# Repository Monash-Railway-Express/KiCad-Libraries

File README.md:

# KiCad-Libraries
To add the footprint library, go to Assign footprints ->  Manage footprint libraries -> Add existing library and select the MREx.pretty folder. Alternatively, from the main KiCad project go to Preferences ->  Manage footprint libraries -> Add existing library and select the MREx.pretty folder. The library “MREx” will then appear in the footprint library list and you will be able to access its footprints in Assign footprints. When updates are made to the library, pull origin in the cloned repo (clone this repo) and KiCad will use the updated library automatically.

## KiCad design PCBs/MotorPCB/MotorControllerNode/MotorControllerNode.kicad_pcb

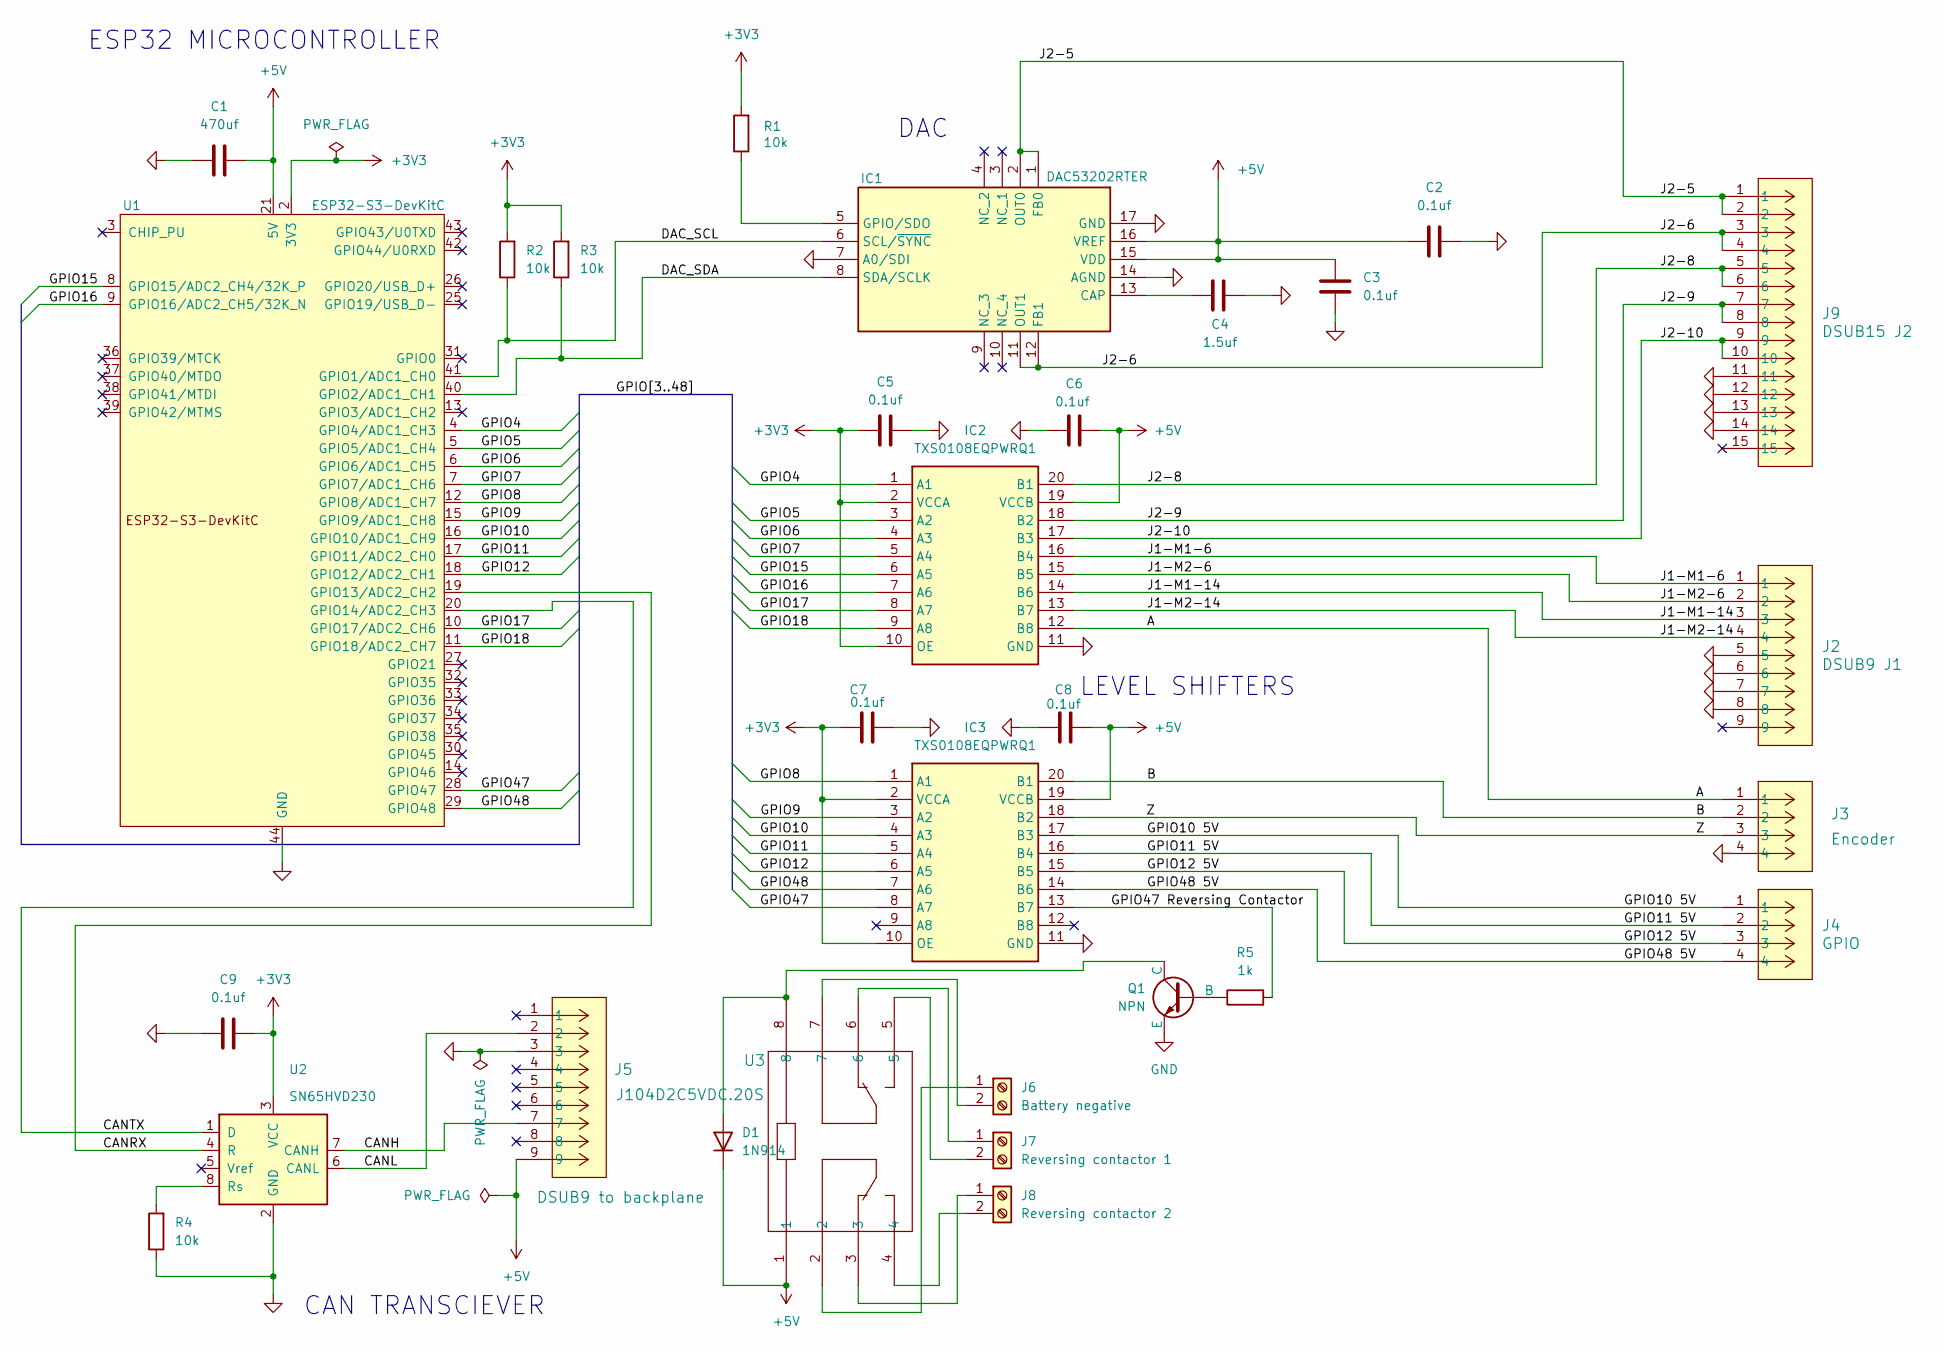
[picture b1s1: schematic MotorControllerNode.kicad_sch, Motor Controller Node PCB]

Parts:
C1: 470uf; C_Radial_D8.0mm_H11.5mm_P3.50mm
C2, C3, C5, C6, C7, C8, C9: 0.1uf; C_0603_1608Metric
C4: 1.5uf; C_0603_1608Metric
D1: 1N914; D_DO-35_SOD27_P7.62mm_Horizontal
IC1: DAC53202RTER; Texas_RTE0016D_WQFN-16-1EP_3x3mm_P0.5mm_EP0.8x0.8mm; Manufacturer_Part_Number DAC53202RTER; Mouser Part Number 595-DAC53202RTER
IC2, IC3: TXS0108EQPWRQ1; SOP65P640X120-20N; Manufacturer_Part_Number TXS0108EQPWRQ1; Mouser Part Number 595-TXS0108EQPWRQ1
J2: DSUB9 J1; DSUB9_FEMALE_RIGHT-ANGLE-THT_2301844-1_TEC
J3: Encoder; SCREW-TERMINAL_2.54mm_1725672_PXC
J4: GPIO; SCREW-TERMINAL_2.54mm_1725672_PXC
J5: DSUB9 to backplane; DSUB9_FEMALE_RIGHT-ANGLE-THT_2301844-1_TEC
J6: Battery negative; TerminalBlock_CUI_TB007-508-02_1x02_P5.08mm_Horizontal
J7: Reversing contactor 1; TerminalBlock_CUI_TB007-508-02_1x02_P5.08mm_Horizontal
J8: Reversing contactor 2; TerminalBlock_CUI_TB007-508-02_1x02_P5.08mm_Horizontal
J9: DSUB15 J2; DSUB15_FEMALE_RIGHT-ANGLE-THT_A-HDF15A-KG-TAXB
Q1: NPN; TO-92
R1, R2, R3, R4: 10k; R_0603_1608Metric
R5: 1k; R_0603_1608Metric_Pad0.98x0.95mm_HandSolder
U1: ESP32-S3-DevKitC
U2: SN65HVD230; SOIC-8_3.9x4.9mm_P1.27mm
U3: J104D2C5VDC.20S; RELAY8_J104D2C5VDC.20S_CRS

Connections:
+3V3: C5.1, C7.1, C9.2, IC2.2 (VCCA), IC2.10 (OE), IC3.2 (VCCA), IC3.10 (OE), R1.2, R2.2, R3.2, U1.1 (3V3), U1.2 (3V3), U2.3 (VCC)
+5V: C1.2, C2.1, C3.1, C6.2, C8.2, D1.1 (K), IC1.15 (VDD), IC1.16 (VREF), IC2.19 (VCCB), IC3.19 (VCCB), J5.9, U1.21 (5V), U3.1
/A: IC2.12 (B8), J3.1
/B: IC3.20 (B1), J3.2
/CANH: J5.7, U2.7 (CANH)
/CANL: J5.2, U2.6 (CANL)
/CANRX: U1.19 (GPIO13/ADC2_CH2), U2.4 (R)
/CANTX: U1.20 (GPIO14/ADC2_CH3), U2.1 (D)
/DAC_SCL: IC1.6 (SCL/~SYNC), R2.1, U1.41 (GPIO1/ADC1_CH0)
/DAC_SDA: IC1.8 (SDA/SCLK), R3.1, U1.40 (GPIO2/ADC1_CH1)
/GPIO4: IC2.1 (A1), U1.4 (GPIO4/ADC1_CH3)
/GPIO5: IC2.3 (A2), U1.5 (GPIO5/ADC1_CH4)
/GPIO6: IC2.4 (A3), U1.6 (GPIO6/ADC1_CH5)
/GPIO7: IC2.5 (A4), U1.7 (GPIO7/ADC1_CH6)
/GPIO8: IC3.1 (A1), U1.12 (GPIO8/ADC1_CH7)
/GPIO9: IC3.3 (A2), U1.15 (GPIO9/ADC1_CH8)
/GPIO10: IC3.4 (A3), U1.16 (GPIO10/ADC1_CH9)
/GPIO10 5V: IC3.17 (B3), J4.1
/GPIO11: IC3.5 (A4), U1.17 (GPIO11/ADC2_CH0)
/GPIO11 5V: IC3.16 (B4), J4.2
/GPIO12: IC3.6 (A5), U1.18 (GPIO12/ADC2_CH1)
/GPIO12 5V: IC3.15 (B5), J4.3
/GPIO15: IC2.6 (A5), U1.8 (GPIO15/ADC2_CH4/32K_P)
/GPIO16: IC2.7 (A6), U1.9 (GPIO16/ADC2_CH5/32K_N)
/GPIO17: IC2.8 (A7), U1.10 (GPIO17/ADC2_CH6)
/GPIO18: IC2.9 (A8), U1.11 (GPIO18/ADC2_CH7)
/GPIO47: IC3.8 (A7), U1.28 (GPIO47)
/GPIO47 Reversing Contactor: IC3.13 (B7), R5.2
/GPIO48: IC3.7 (A6), U1.29 (GPIO48)
/GPIO48 5V: IC3.14 (B6), J4.4
/J1-M1-6: IC2.16 (B4), J2.1
/J1-M1-14: IC2.14 (B6), J2.3
/J1-M2-6: IC2.15 (B5), J2.2
/J1-M2-14: IC2.13 (B7), J2.4
/J2-5: IC1.1 (FB0), IC1.2 (OUT0), J9.1, J9.2
/J2-6: IC1.11 (OUT1), IC1.12 (FB1), J9.3, J9.4
/J2-8: IC2.20 (B1), J9.5, J9.6
/J2-9: IC2.18 (B2), J9.7, J9.8
/J2-10: IC2.17 (B3), J9.9, J9.10
/Z: IC3.18 (B2), J3.3
GND: C1.1, C2.2, C3.2, C4.1, C5.2, C6.1, C7.2, C8.1, C9.1, IC1.7 (A0/SDI), IC1.14 (AGND), IC1.17 (GND), IC2.11 (GND), IC3.11 (GND), J2.5, J2.6, J2.7, J2.8, J3.4, J5.3, J9.11, J9.12, J9.13, J9.14, Q1.1 (E), R4.1, U1.22 (GND), U1.23 (GND), U1.24 (GND), U1.44 (GND), U2.2 (GND)
unnamed: D1.2 (A), Q1.3 (C), U3.8
unnamed: C4.2, IC1.13 (CAP)
unnamed: IC1.5 (GPIO/SDO), R1.1
unnamed: J6.1, U3.2
unnamed: J6.2, U3.7
unnamed: J7.1, U3.6
unnamed: J7.2, U3.5
unnamed: J8.1, U3.3
unnamed: J8.2, U3.4
unnamed: Q1.2 (B), R5.1
unnamed: R4.2, U2.8 (Rs)

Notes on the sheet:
LEVEL SHIFTERS
CAN TRANSCIEVER
DAC
ESP32 MICROCONTROLLER

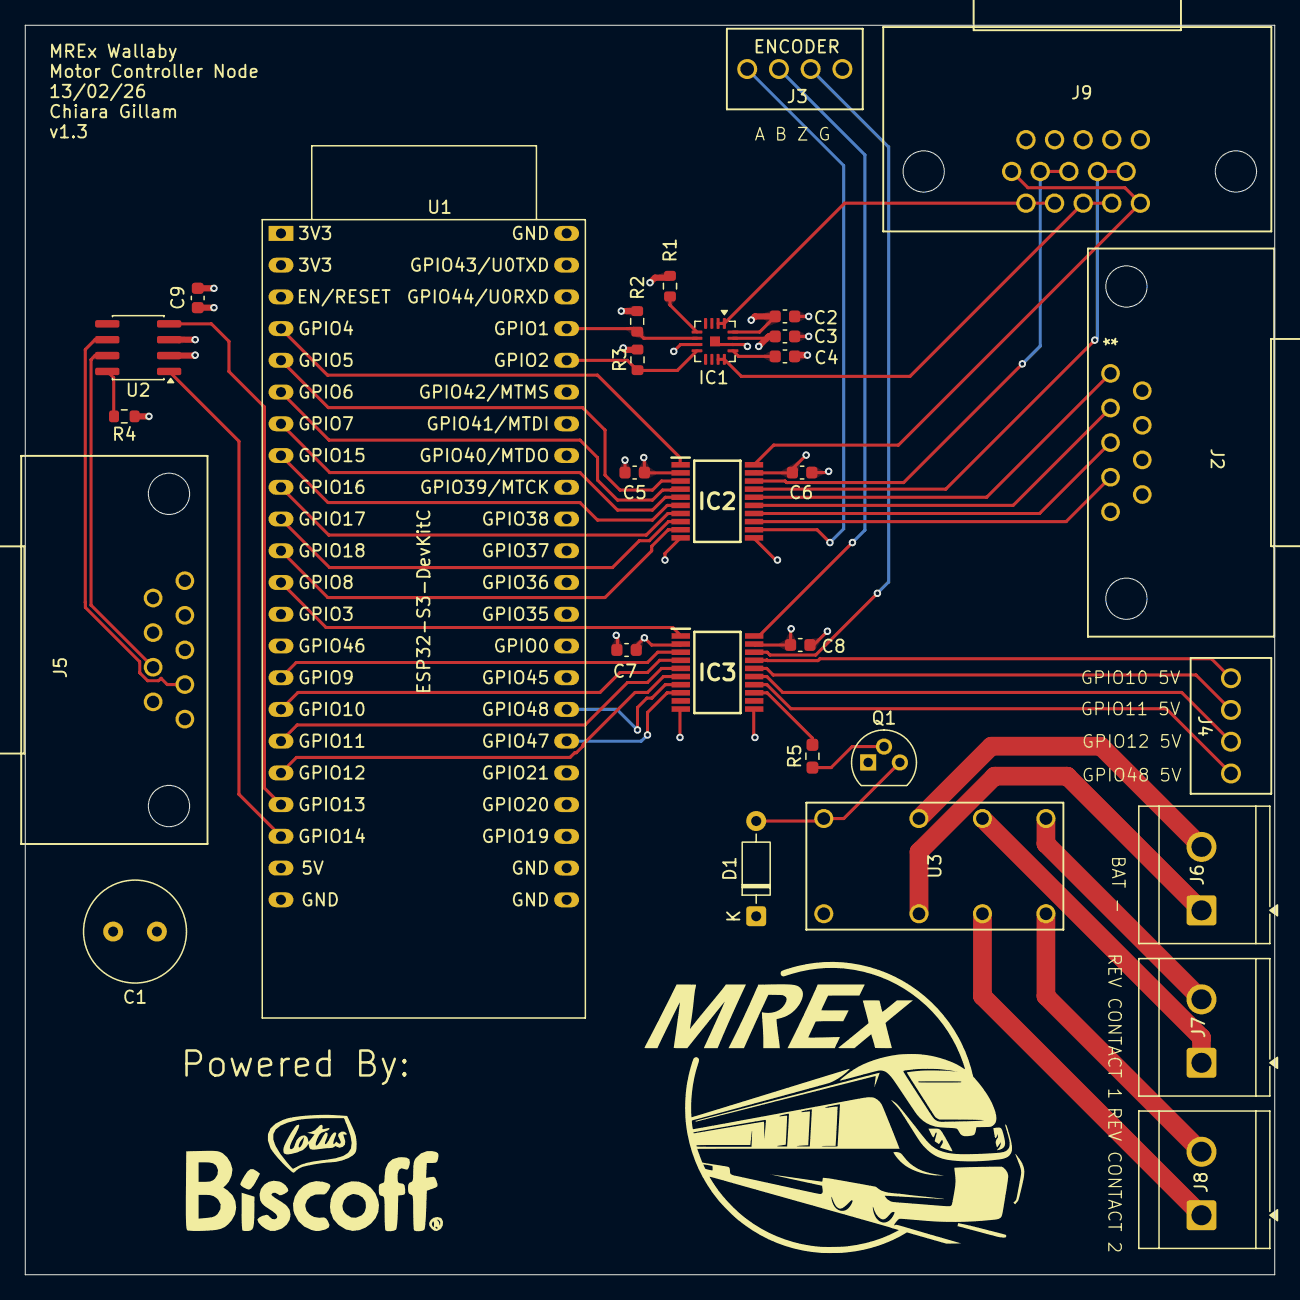
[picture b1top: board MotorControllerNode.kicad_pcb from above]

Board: 4 copper layers, 100.0 x 100.0 mm, 30 parts (0 on the bottom side), 52 nets.

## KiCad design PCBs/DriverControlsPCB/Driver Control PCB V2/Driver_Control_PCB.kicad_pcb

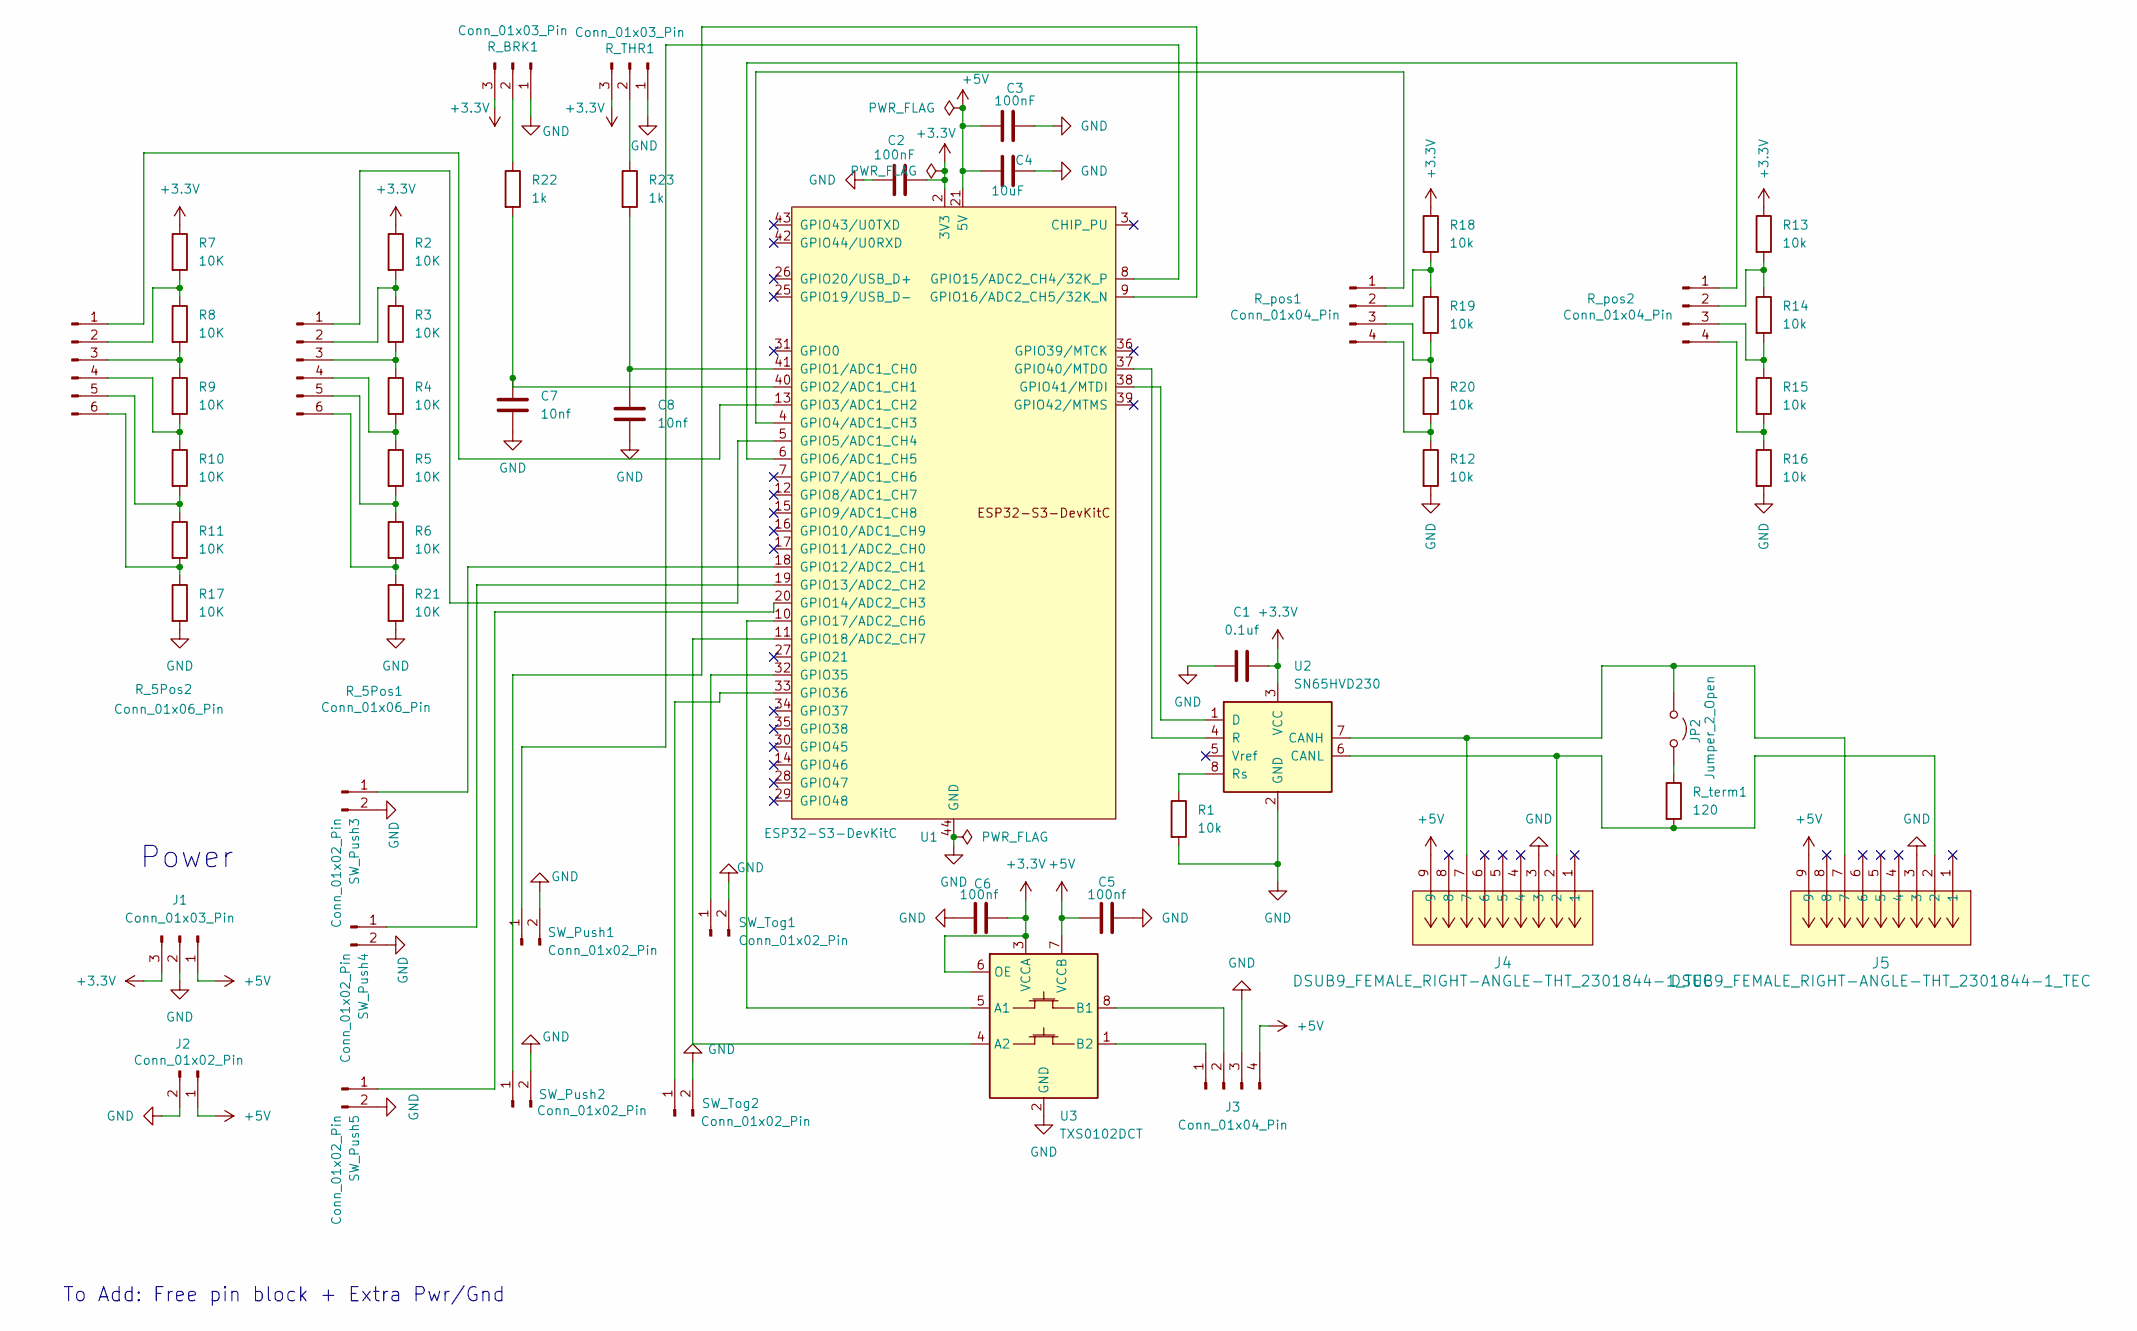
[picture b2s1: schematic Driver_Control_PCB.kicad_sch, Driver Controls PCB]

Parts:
C1: 0.1uf; C_0805_2012Metric
C2, C3: 100nF; C_0805_2012Metric
C4: 10uF; C_0805_2012Metric
C5, C6: 100nf; C_0805_2012Metric
C7, C8: 10nf; C_0805_2012Metric
J1: Conn_01x03_Pin; Altech_AK100_1x03_P5.00mm
J2: Conn_01x02_Pin; Altech_AK100_1x02_P5.00mm
J3: Conn_01x04_Pin; JST_GH_SM04B-GHS-TB_1x04-1MP_P1.25mm_Horizontal
J4, J5: DSUB9_FEMALE_RIGHT-ANGLE-THT_2301844-1_TEC
JP2: Jumper_2_Open; PinHeader_1x02_P2.54mm_Vertical
R1, R12, R13, R14, R15, R16, R18, R19, R20: 10k; R_0805_2012Metric
R2, R3, R4, R5, R6, R7, R8, R9, R10, R11, R17, R21: 10K; R_0805_2012Metric
R22, R23: 1k; R_0805_2012Metric
R_5Pos1, R_5Pos2: Conn_01x06_Pin; JST_GH_SM06B-GHS-TB_1x06-1MP_P1.25mm_Horizontal
R_BRK1: Conn_01x03_Pin; JST_GH_SM03B-GHS-TB_1x03-1MP_P1.25mm_Horizontal
R_THR1: Conn_01x03_Pin; JST_GH_SM03B-GHS-TB_1x03-1MP_P1.25mm_Horizontal
R_pos1, R_pos2: Conn_01x04_Pin; JST_GH_SM04B-GHS-TB_1x04-1MP_P1.25mm_Horizontal
R_term1: 120; R_0805_2012Metric
SW_Push1, SW_Push2, SW_Push3, SW_Push4, SW_Push5: Conn_01x02_Pin; JST_GH_SM02B-GHS-TB_1x02-1MP_P1.25mm_Horizontal
SW_Tog1, SW_Tog2: Conn_01x02_Pin; JST_GH_SM02B-GHS-TB_1x02-1MP_P1.25mm_Horizontal
U1: ESP32-S3-DevKitC
U2: SN65HVD230; SOIC-8_3.9x4.9mm_P1.27mm
U3: TXS0102DCT; SSOP-8_2.95x2.8mm_P0.65mm

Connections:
+3.3V: C1.2, C2.2, C6.2, J1.3, R2.1, R7.1, R13.1, R18.1, R_BRK1.3, R_THR1.3, U1.1 (3V3), U1.2 (3V3), U2.3 (VCC), U3.3 (VCCA), U3.6 (OE)
+5V: C3.1, C4.1, C5.1, J1.1, J2.1, J3.4, J4.9, J5.9, U1.21 (5V), U3.7 (VCCB)
GND: C1.1, C2.1, C3.2, C4.2, C5.2, C6.1, C7.2, C8.2, J1.2, J2.2, J3.3, J4.3, J5.3, R1.2, R12.2, R16.2, R17.2, R21.2, R_BRK1.1, R_THR1.1, SW_Push1.2, SW_Push2.2, SW_Push3.2, SW_Push4.2, SW_Push5.2, SW_Tog1.2, SW_Tog2.2, U1.22 (GND), U1.23 (GND), U1.24 (GND), U1.44 (GND), U2.2 (GND), U3.2 (GND)
unnamed: J3.1, U3.1 (B2)
unnamed: J3.2, U3.8 (B1)
unnamed: J4.7, J5.7, JP2.1 (A), U2.7 (CANH)
unnamed: JP2.2 (B), R_term1.1
unnamed: R_5Pos1.1, U1.5 (GPIO5/ADC1_CH4)
unnamed: R2.2, R3.1, R_5Pos1.2
unnamed: R3.2, R4.1, R_5Pos1.3
unnamed: R4.2, R5.1, R_5Pos1.4
unnamed: R5.2, R6.1, R_5Pos1.5
unnamed: R6.2, R21.1, R_5Pos1.6
unnamed: R_5Pos2.1, U1.13 (GPIO3/ADC1_CH2)
unnamed: R7.2, R8.1, R_5Pos2.2
unnamed: R8.2, R9.1, R_5Pos2.3
unnamed: R9.2, R10.1, R_5Pos2.4
unnamed: R10.2, R11.1, R_5Pos2.5
unnamed: R11.2, R17.1, R_5Pos2.6
unnamed: R22.1, R_BRK1.2
unnamed: R23.1, R_THR1.2
unnamed: R_pos1.1, U1.4 (GPIO4/ADC1_CH3)
unnamed: R18.2, R19.1, R_pos1.2
unnamed: R19.2, R20.1, R_pos1.3
unnamed: R12.1, R20.2, R_pos1.4
unnamed: R_pos2.1, U1.6 (GPIO6/ADC1_CH5)
unnamed: R13.2, R14.1, R_pos2.2
unnamed: R14.2, R15.1, R_pos2.3
unnamed: R15.2, R16.1, R_pos2.4
unnamed: SW_Push1.1, U1.8 (GPIO15/ADC2_CH4/32K_P)
unnamed: SW_Push2.1, U1.9 (GPIO16/ADC2_CH5/32K_N)
unnamed: SW_Push3.1, U1.18 (GPIO12/ADC2_CH1)
unnamed: SW_Push4.1, U1.19 (GPIO13/ADC2_CH2)
unnamed: SW_Push5.1, U1.20 (GPIO14/ADC2_CH3)
unnamed: SW_Tog1.1, U1.32 (GPIO35)
unnamed: SW_Tog2.1, U1.33 (GPIO36)
unnamed: C8.1, R23.2, U1.41 (GPIO1/ADC1_CH0)
unnamed: C7.1, R22.2, U1.40 (GPIO2/ADC1_CH1)
unnamed: U1.10 (GPIO17/ADC2_CH6), U3.5 (A1)
unnamed: U1.11 (GPIO18/ADC2_CH7), U3.4 (A2)
unnamed: U1.37 (GPIO40/MTDO), U2.4 (R)
unnamed: U1.38 (GPIO41/MTDI), U2.1 (D)
unnamed: J4.2, J5.2, R_term1.2, U2.6 (CANL)
unnamed: R1.1, U2.8 (Rs)

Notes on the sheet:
To Add: Free pin block + Extra Pwr/Gnd
Power

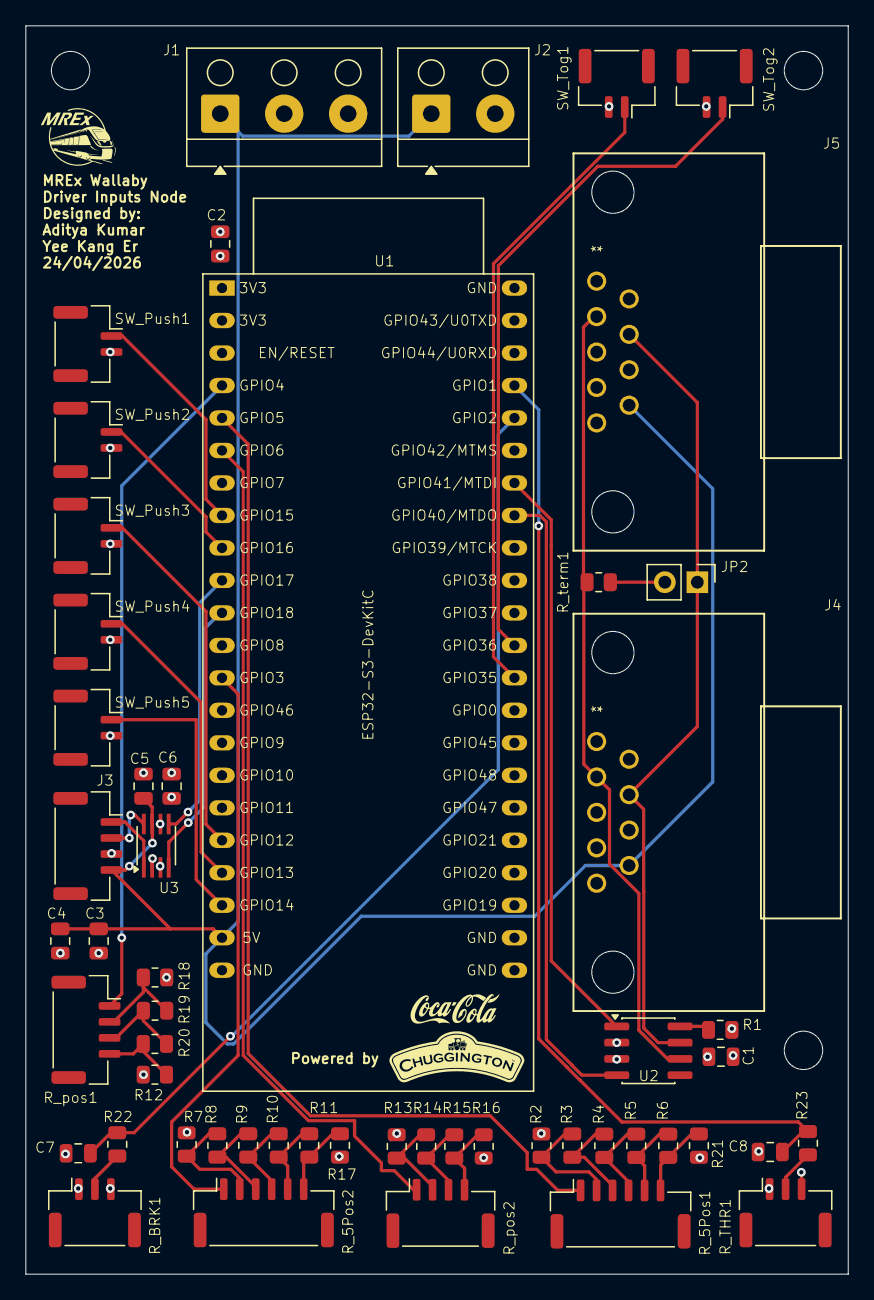
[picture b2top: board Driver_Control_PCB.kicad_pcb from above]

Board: 4 copper layers, 64.3 x 97.6 mm, 54 parts (0 on the bottom side), 44 nets.

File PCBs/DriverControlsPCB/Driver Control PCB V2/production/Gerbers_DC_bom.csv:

Designator,Footprint,Quantity,Value,LCSC Part #
C1,0805,1,0.1uf,
"C2, C3, C5, C6",0805,4,100nF,
C4,0805,1,10uF,
"C7, C8",0805,2,10nf,
J1,Altech_AK100_1x03_P5.00mm,1,Conn_01x03_Pin,
J2,Altech_AK100_1x02_P5.00mm,1,Conn_01x02_Pin,
"J3, R_POS1, R_POS2",JST_GH_SM04B-GHS-TB_1x04-1MP_P1.25mm_Horizontal,3,Conn_01x04_Pin,
"J4, J5",DSUB9_FEMALE_RIGHT-ANGLE-THT_2301844-1_TEC,2,DSUB9_FEMALE_RIGHT-ANGLE-THT_2301844-1_TEC,
JP2,PinHeader_1x02_P2.54mm_Vertical,1,Jumper_2_Open,
"R1, R10, R11, R12, R13, R14, R15, R16, R17, R18, R19, R2, R20, R21, R3, R4, R5, R6, R7, R8, R9",0805,21,10k,
"R22, R23",0805,2,1k,
"R_5POS1, R_5POS2",JST_GH_SM06B-GHS-TB_1x06-1MP_P1.25mm_Horizontal,2,Conn_01x06_Pin,
"R_BRK1, R_THR1",JST_GH_SM03B-GHS-TB_1x03-1MP_P1.25mm_Horizontal,2,Conn_01x03_Pin,
R_TERM1,0805,1,120,
"SW_PUSH1, SW_PUSH2, SW_PUSH3, SW_PUSH4, SW_PUSH5, SW_TOG1, SW_TOG2",JST_GH_SM02B-GHS-TB_1x02-1MP_P1.25mm_Horizontal,7,Conn_01x02_Pin,
U1,ESP32-S3-DevKitC,1,ESP32-S3-DevKitC,
U2,SOIC-8_3.9x4.9mm_P1.27mm,1,SN65HVD230,
U3,SSOP-8_2.95x2.8mm_P0.65mm,1,TXS0102DCT,

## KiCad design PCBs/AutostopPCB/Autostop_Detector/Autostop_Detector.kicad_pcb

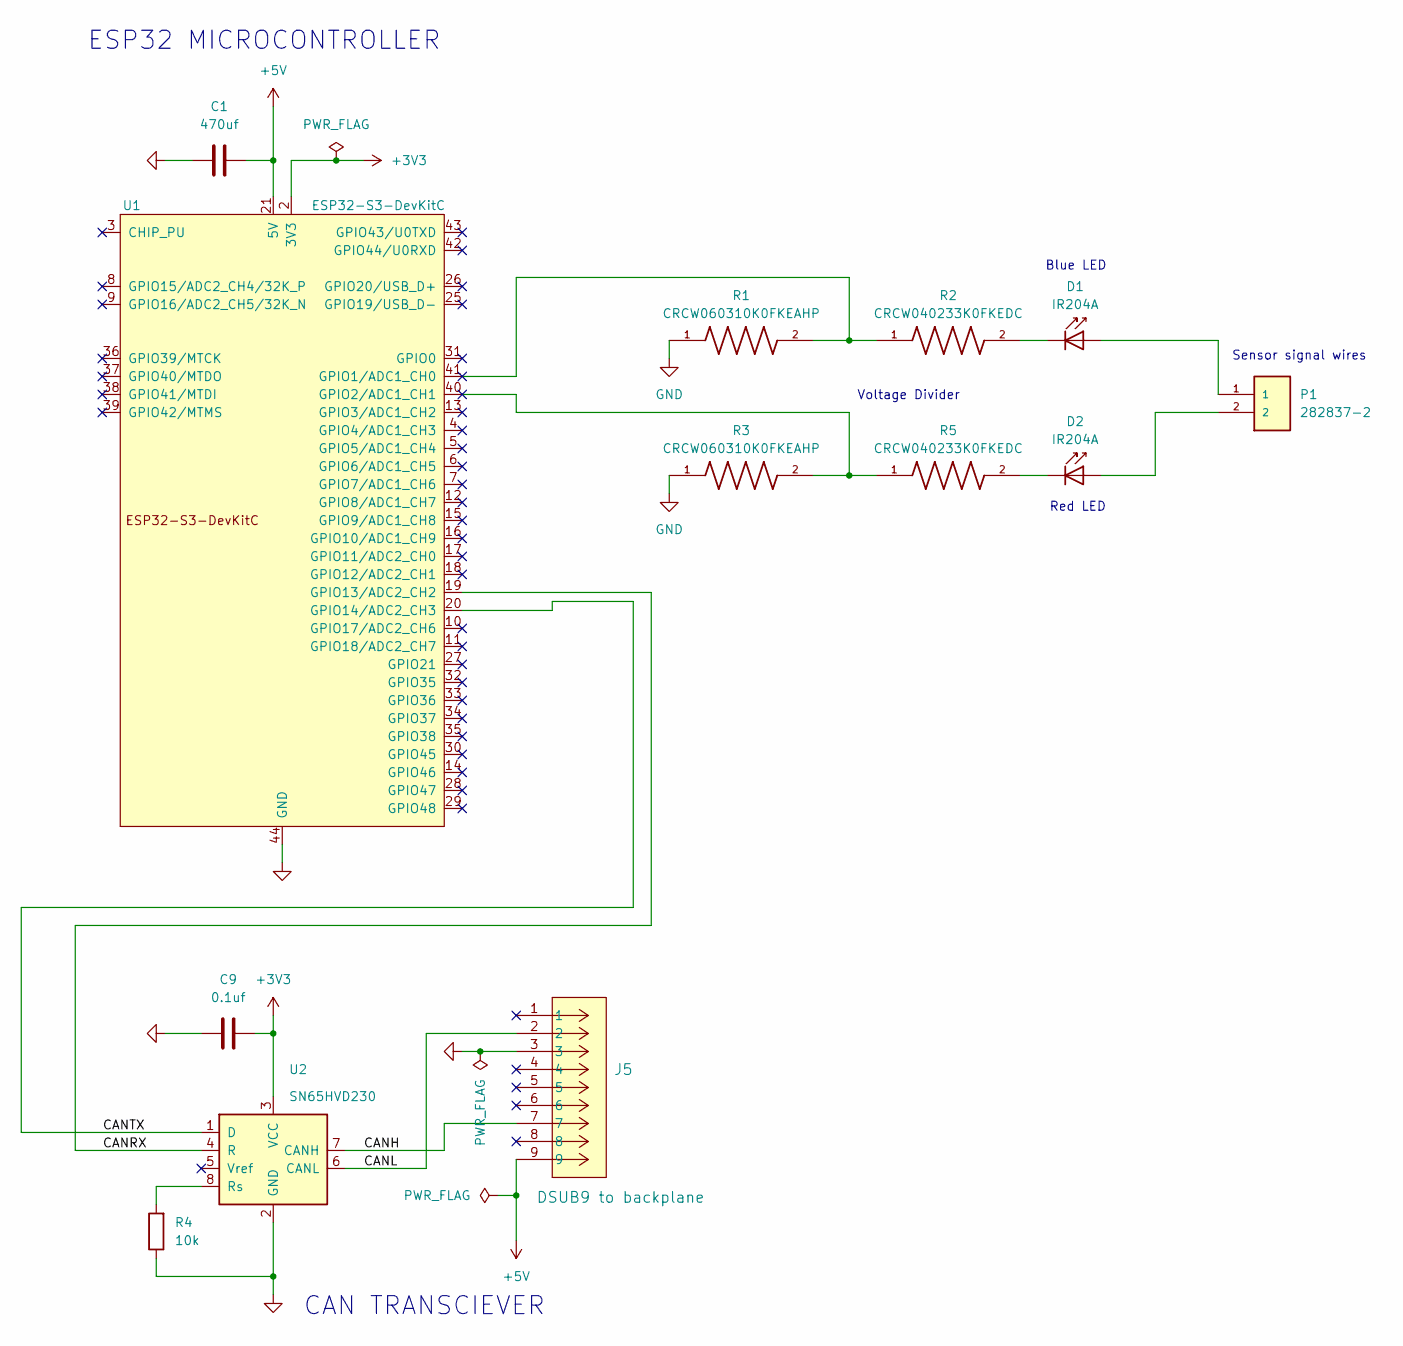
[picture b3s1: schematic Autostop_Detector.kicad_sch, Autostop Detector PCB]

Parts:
C1: 470uf; C_Radial_D8.0mm_H11.5mm_P3.50mm
C9: 0.1uf; C_0603_1608Metric
D1, D2: IR204A; LED_D3.0mm_IRBlack
J5: DSUB9 to backplane; DSUB9_FEMALE_RIGHT-ANGLE-THT_2301844-1_TEC
P1: 282837-2; TE_282837-2; PARTREV G3
R1, R3: CRCW060310K0FKEAHP; RESC1608X55N
R2, R5: CRCW040233K0FKEDC; RESC1005X35N
R4: 10k; R_0603_1608Metric
U1: ESP32-S3-DevKitC
U2: SN65HVD230; SOIC-8_3.9x4.9mm_P1.27mm

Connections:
+3V3: C9.2, U1.1 (3V3), U1.2 (3V3), U2.3 (VCC)
+5V: C1.2, J5.9, U1.21 (5V)
/CANH: J5.7, U2.7 (CANH)
/CANL: J5.2, U2.6 (CANL)
/CANRX: U1.19 (GPIO13/ADC2_CH2), U2.4 (R)
/CANTX: U1.20 (GPIO14/ADC2_CH3), U2.1 (D)
GND: C1.1, C9.1, J5.3, R1.1, R3.1, R4.1, U1.22 (GND), U1.23 (GND), U1.24 (GND), U1.44 (GND), U2.2 (GND)
unnamed: D1.2 (A), P1.1
unnamed: D1.1 (K), R2.2
unnamed: D2.2 (A), P1.2
unnamed: D2.1 (K), R5.2
unnamed: R1.2, R2.1, U1.41 (GPIO1/ADC1_CH0)
unnamed: R3.2, R5.1, U1.40 (GPIO2/ADC1_CH1)
unnamed: R4.2, U2.8 (Rs)

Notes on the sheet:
Blue LED
Voltage Divider
Sensor signal wires
CAN TRANSCIEVER
Red LED
ESP32 MICROCONTROLLER

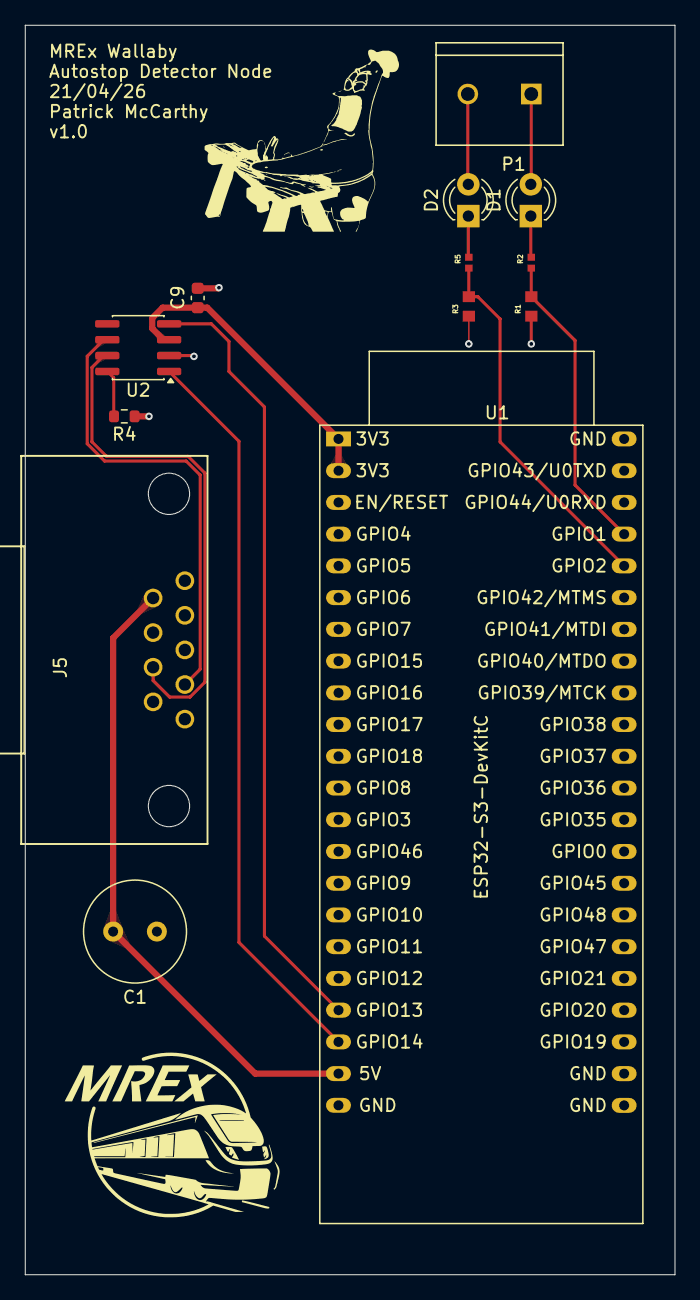
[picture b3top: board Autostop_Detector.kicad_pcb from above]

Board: 2 copper layers, 52.0 x 100.0 mm, 13 parts (0 on the bottom side), 14 nets.

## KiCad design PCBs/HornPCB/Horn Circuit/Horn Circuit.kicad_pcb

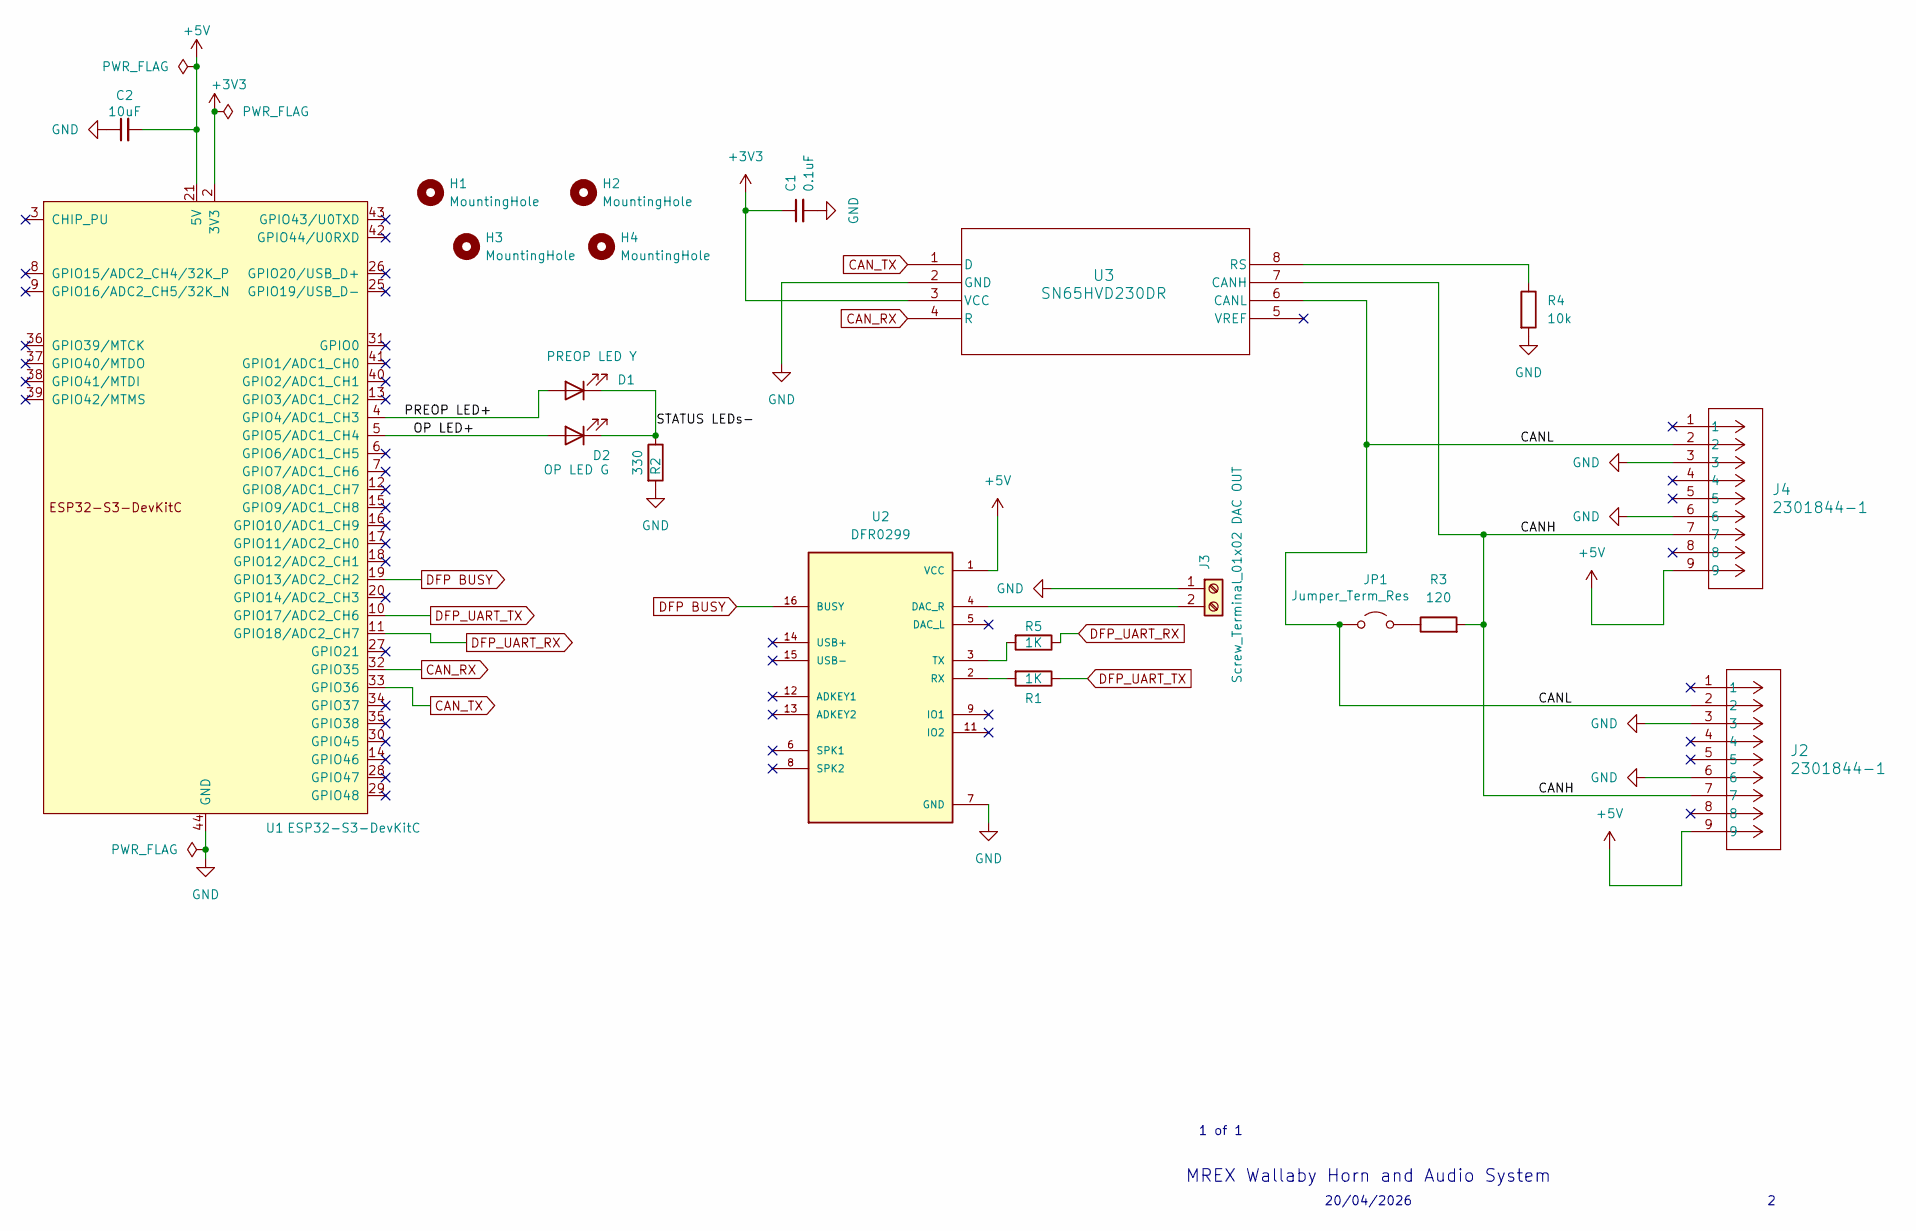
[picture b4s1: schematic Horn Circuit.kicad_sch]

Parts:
C1: 0.1uF; C_0603_1608Metric
C2: 10uF; C_0805_2012Metric
D1: PREOP LED Y; LED_D5.0mm
D2: OP LED G; LED_D5.0mm
H1, H2, H3, H4: MountingHole; MountingHole_3.2mm_M3
J2, J4: 2301844-1; DSUB9_FEMALE_RIGHT-ANGLE-THT_2301844-1_TEC
J3: Screw_Terminal_01x02 DAC OUT; TerminalBlock_Phoenix_MKDS-1,5-2-5.08_1x02_P5.08mm_Horizont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
JP1: Jumper_Term_Res; PinHeader_1x02_P2.54mm_Vertical
R1, R5: 1K; R_Axial_DIN0207_L6.3mm_D2.5mm_P7.62mm_Horizontal
R2: 330; R_Axial_DIN0207_L6.3mm_D2.5mm_P7.62mm_Horizontal
R3: 120; R_Axial_DIN0207_L6.3mm_D2.5mm_P7.62mm_Horizontal
R4: 10k; R_0603_1608Metric
U1: ESP32-S3-DevKitC
U2: DFR0299; MODULE_DFR0299
U3: SN65HVD230DR; D8

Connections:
+3V3: C1.1, U1.1 (3V3), U1.2 (3V3), U3.3 (VCC)
+5V: C2.2, J2.9, J4.9, U1.21 (5V), U2.1 (VCC)
/CANH: J2.7, J4.7, R3.2, U3.7 (CANH)
/CANL: J2.2, J4.2, JP1.1 (A), U3.6 (CANL)
/DAC_R+: J3.2, U2.4 (DAC_R)
/OP LED+: D2.2 (A), U1.5 (GPIO5/ADC1_CH4)
/PREOP LED+: D1.2 (A), U1.4 (GPIO4/ADC1_CH3)
/STATUS LEDs-: D1.1 (K), D2.1 (K), R2.1
CAN_RX: U1.32 (GPIO35), U3.4 (R)
CAN_TX: U1.33 (GPIO36), U3.1 (D)
DFP BUSY: U1.19 (GPIO13/ADC2_CH2), U2.16 (BUSY)
DFP_UART_RX: R5.1, U1.11 (GPIO18/ADC2_CH7)
DFP_UART_TX: R1.1, U1.10 (GPIO17/ADC2_CH6)
GND: C1.2, C2.1, J2.3, J2.6, J3.1, J4.3, J4.6, R2.2, R4.2, U1.22 (GND), U1.23 (GND), U1.24 (GND), U1.44 (GND), U2.7 (GND), U2.10 (GND), U3.2 (GND)
unnamed: JP1.2 (B), R3.1
unnamed: R1.2, U2.2 (RX)
unnamed: R5.2, U2.3 (TX)
unnamed: R4.1, U3.8 (RS)

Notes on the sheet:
20/04/2026
1 of 1
MREX Wallaby Horn and Audio System

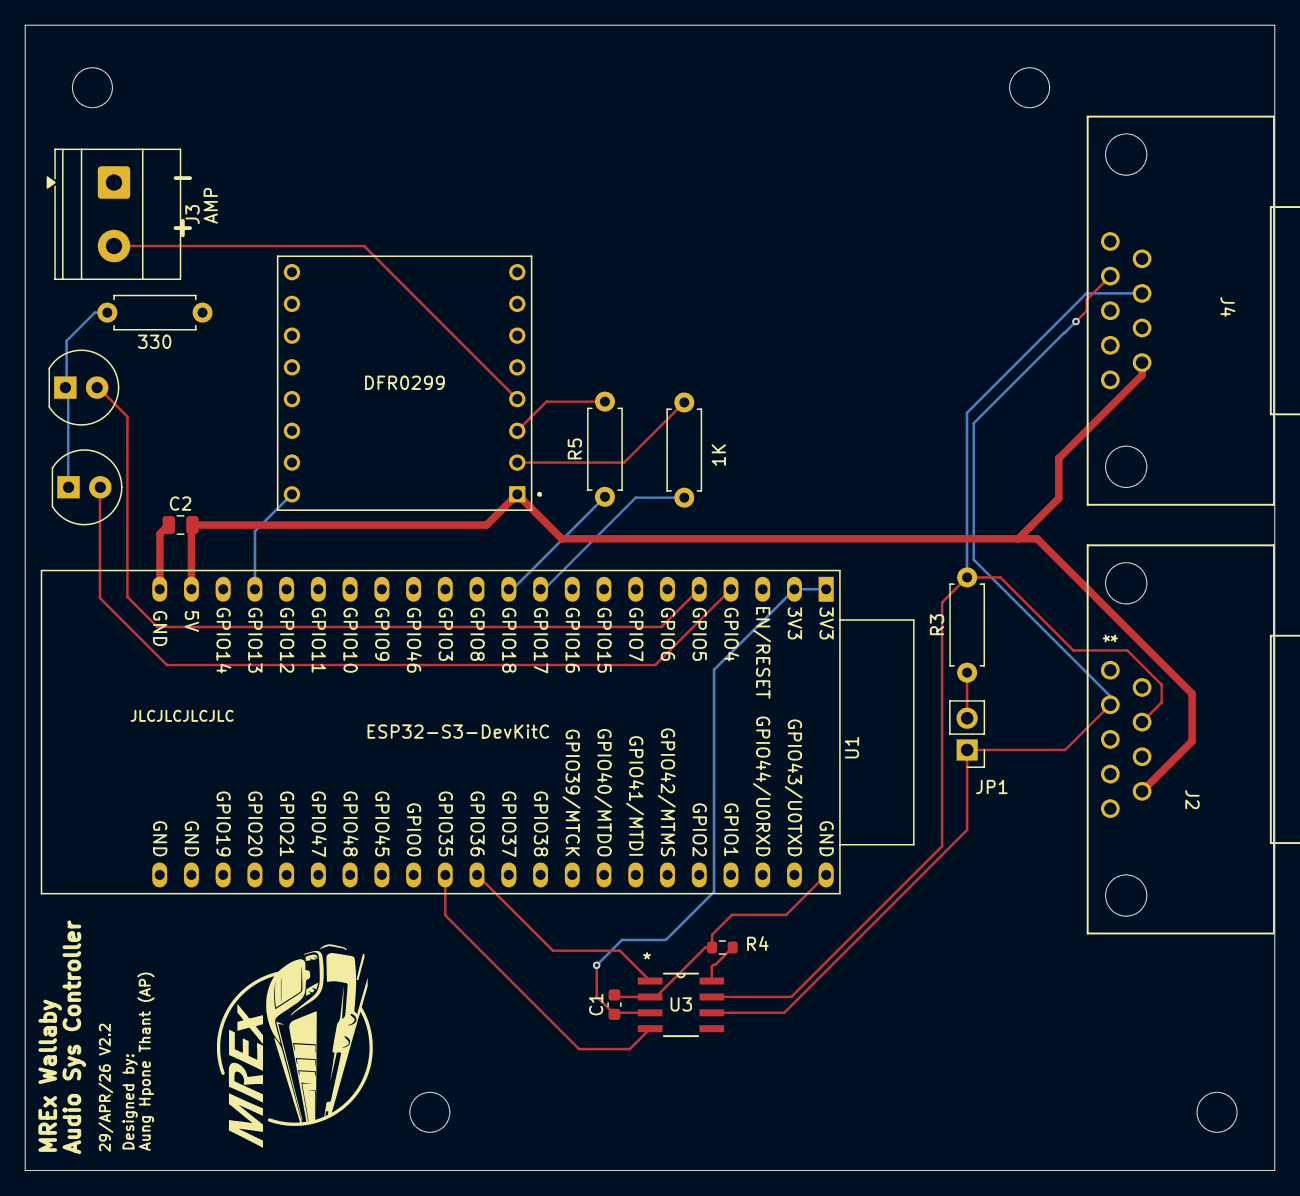
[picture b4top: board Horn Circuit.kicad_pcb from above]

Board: 2 copper layers, 100.0 x 91.7 mm, 20 parts (0 on the bottom side), 18 nets.
